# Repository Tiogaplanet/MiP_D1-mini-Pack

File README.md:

# MiP_D1-mini-Pack
A [D1 mini](https://wiki.wemos.cc/products:d1:d1_mini) adapter board for [WowWee Labs'](https://github.com/WowWeeLabs/) [MiP](https://wowwee.com/mip) robot.  Similar to the [MiP ProMini Pack](https://github.com/adamgreen/MiP_ProMini-Pack), this board adapts the D1 mini and compatible boards to MiP.  Either install the D1 mini Pack in a pair of pin headers or solder it directly to the board and you'll be programming MiP to connect to the Internet in no time.

## Acknowledgment
* As always, a big "thank you" goes out to [adamgreen](https://github.com/adamgreen/).  Without his help I'd still be wondering why my MiP won't talk to an Arduino.  Now, it's talking to the Internet!
* I'd also like to thank [Casey Kuhns](https://github.com/caseykuhns) who while at [SparkFun](https://github.com/sparkfun) developed the original [ProMini Pack](https://github.com/sparkfun/mip_promini-pack) and the [ProtoPack](https://github.com/sparkfun/mip_proto-pack) which provided the foundation for this project.

## OSH Park renderings

## Installation
Please see the [wiki](https://github.com/Tiogaplanet/MiP_D1-mini-Pack/wiki) for up-to-date installation instructions.

## Disclaimer
I am a hobbyiest sharing this designed-at-home board with fans of robotics, MiP and the ESP8266 wifi chip.  While I strive to make this board as useful and "right" as it can be, in no way shall I be responsible for any damage that may occur to your MiP or D1 mini either incidently or directly through the use of this board.  You use this board at your own risk.

If you are experienced in robotics or circuit design and spot something that can or should be improved, please review [CONTRIBUTING.md](https://github.com/Tiogaplanet/MiP_D1-mini-Pack/blob/master/CONTRIBUTING.md) and submit a pull request.

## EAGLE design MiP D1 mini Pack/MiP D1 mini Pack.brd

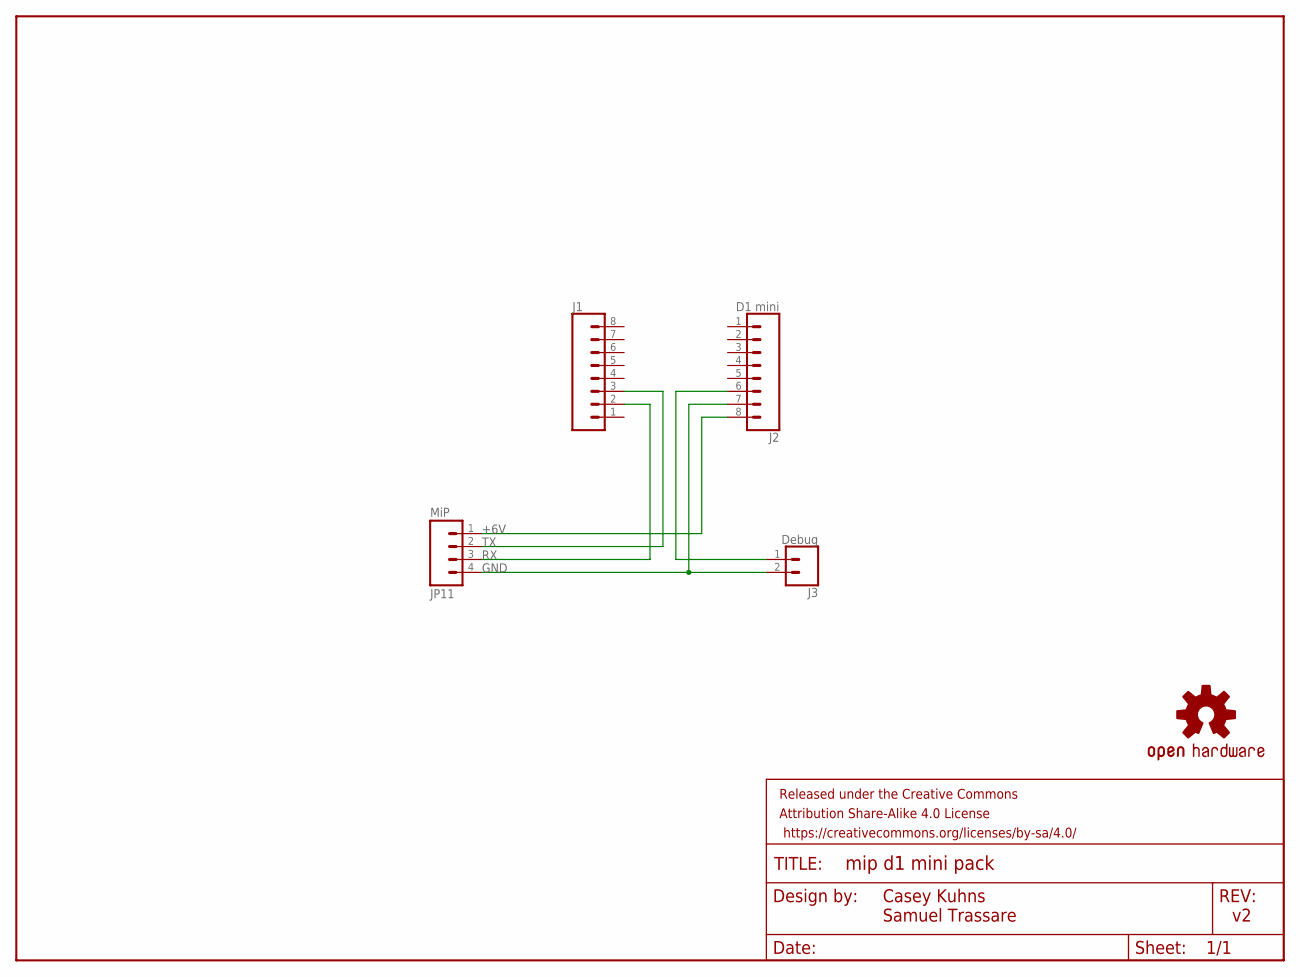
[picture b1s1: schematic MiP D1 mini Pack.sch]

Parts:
FRAME1: FRAME-LETTER; CREATIVE_COMMONS
J1: CONN_08"; 1X08
J2: D1 mini; 1X08
J3: Debug; 1X02_RA_PTH_FEMALE
JP11: MiP; 1X04-1.5MM_JST
LOGO2: OSHW-LOGOS; OSHW-LOGO-S

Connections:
+6V: J2.8, JP11.1
DEBUG: J2.6, J3.1
GND: J2.7, J3.2, JP11.4
RX: J1.2, JP11.3
TX: J1.3, JP11.2

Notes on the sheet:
Casey Kuhns Samuel Trassare

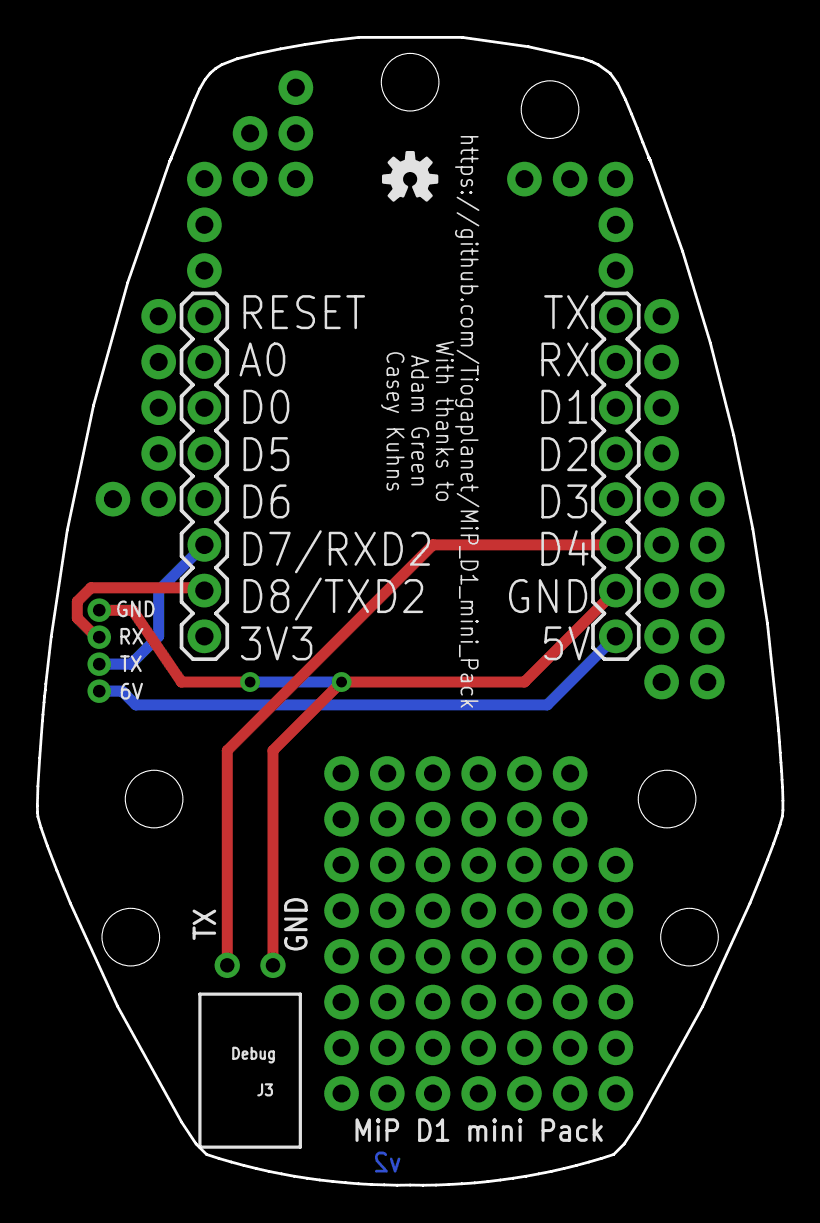
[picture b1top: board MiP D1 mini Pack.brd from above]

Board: 2 copper layers, 41.4 x 63.8 mm, 6 parts (1 on the bottom side), 5 nets.

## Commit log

2018-08-08 Initial commit of eagle files.
2018-08-08 Added OSH Park images.
2018-08-08 Added images to readme
2018-08-08 Moved the debug connector
2018-08-10 Added note about installation (see the wiki)
2018-08-25 Fixed rookie mistake (RX/TX was backwards)
    Fixed twisted RX/TX pair, corrected labels, added labels for debug
    connector, made minor moves.
2018-08-25 Added net classes for RX and TX.
2018-08-25 Updated the OSH Park renderings
2018-08-25 Updated links for OSH Park renderings.
2018-08-25 Undo link updates on OSH Park renderings.
2018-10-08 Fixed breadboard holes
    Several breadboad holes had been accidentally connected.
2018-10-08 Deleted more connected vias

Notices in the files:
parts and their libraries:
SparkFun-Aesthetics: Licensing: Creative Commons ShareAlike 4.0 International - https://creativecommons.org/licenses/by-sa/4.0
SparkFun-Aesthetics: Released under the Creative Commons Attribution Share-Alike 4.0 License
SparkFun-Aesthetics: https://creativecommons.org/licenses/by-sa/4.0
